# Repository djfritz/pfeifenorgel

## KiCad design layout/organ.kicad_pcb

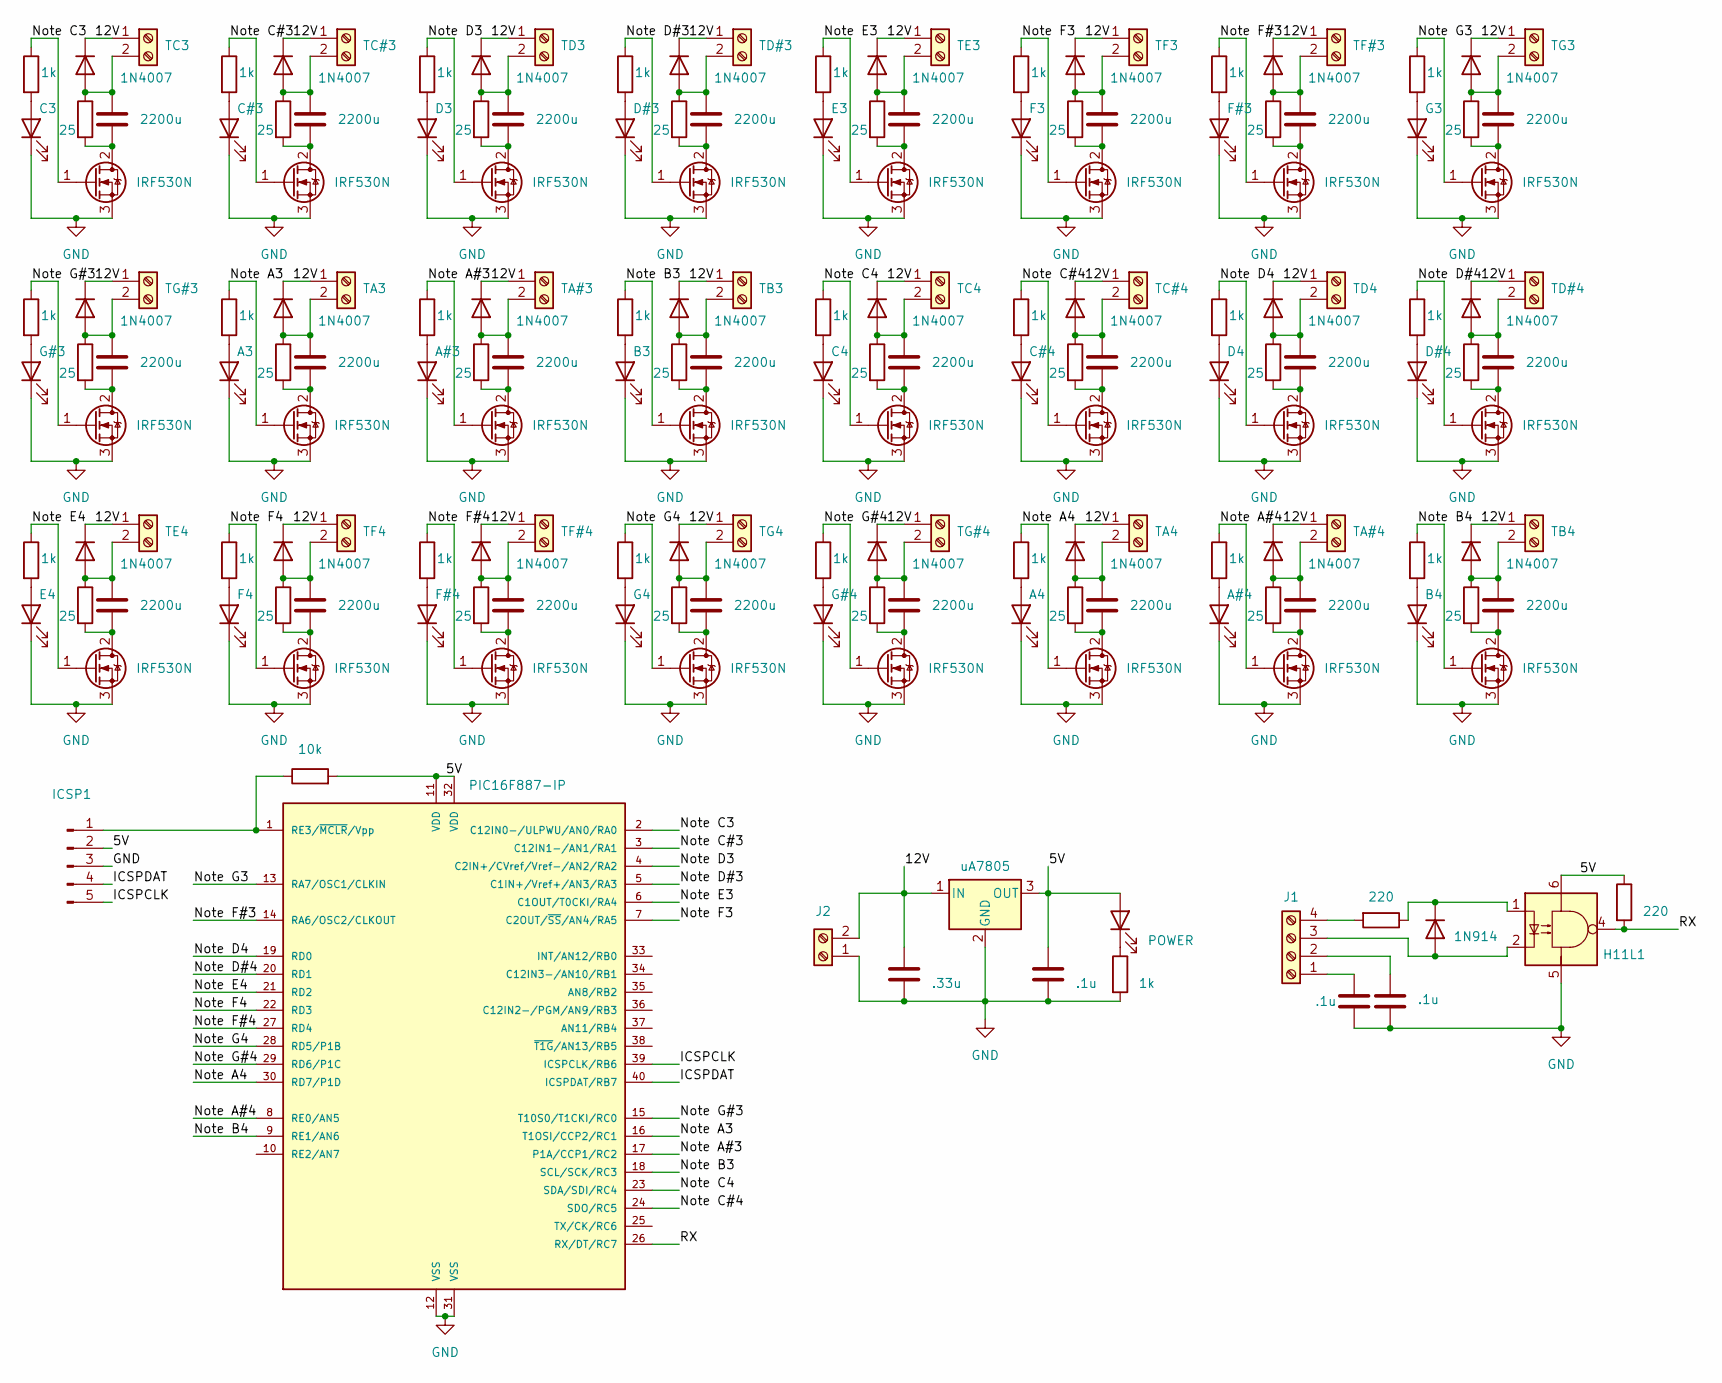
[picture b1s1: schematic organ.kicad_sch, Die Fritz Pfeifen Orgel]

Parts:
C1: .33u; C_Rect_L7.2mm_W3.0mm_P5.00mm_FKS2_FKP2_MKS2_MKP2
C2, C3, C4: .1u; C_Rect_L7.0mm_W2.5mm_P5.00mm
C5, C6, C7, C8, C9, C10, C11, C12, C13, C14, C15, C16, C17, C18, C19, C20, C21, C22, C23, C24, C25, C26, C27, C28: 2200u; C_Radial_D16.0mm_H25.0mm_P7.50mm
D1: 1N914; D_DO-35_SOD27_P7.62mm_Horizontal
D2, D6, D8, D10, D12, D14, D16, D18, D20, D22, D24, D26, D28, D30, D32, D34, D36, D38, D40, D42, D44, D46, D48, D50: 1N4007; D_DO-41_SOD81_P10.16mm_Horizontal
D3: C3; LED_D5.0mm_Clear
D4: POWER; LED_D5.0mm_Clear
D5: C#3; LED_D5.0mm_Clear
D7: D3; LED_D5.0mm_Clear
D9: D#3; LED_D5.0mm_Clear
D11: E3; LED_D5.0mm_Clear
D13: F3; LED_D5.0mm_Clear
D15: F#3; LED_D5.0mm_Clear
D17: G3; LED_D5.0mm_Clear
D19: G#3; LED_D5.0mm_Clear
D21: A3; LED_D5.0mm_Clear
D23: A#3; LED_D5.0mm_Clear
D25: B3; LED_D5.0mm_Clear
D27: C4; LED_D5.0mm_Clear
D29: C#4; LED_D5.0mm_Clear
D31: D4; LED_D5.0mm_Clear
D33: D#4; LED_D5.0mm_Clear
D35: E4; LED_D5.0mm_Clear
D37: F4; LED_D5.0mm_Clear
D39: F#4; LED_D5.0mm_Clear
D41: G4; LED_D5.0mm_Clear
D43: G#4; LED_D5.0mm_Clear
D45: A4; LED_D5.0mm_Clear
D47: A#4; LED_D5.0mm_Clear
D49: B4; LED_D5.0mm_Clear
ICSP1: Conn_01x05_Pin; PinHeader_1x05_P2.54mm_Vertical
J1: Screw_Terminal_01x04; TerminalBlock_RND_205-00003_1x04_P5.00mm_Horizontal
J2: Screw_Terminal_01x02; TerminalBlock_RND_205-00001_1x02_P5.00mm_Horizontal
Q1, Q2, Q3, Q4, Q5, Q6, Q7, Q8, Q9, Q10, Q11, Q12, Q13, Q14, Q15, Q16, Q17, Q18, Q19, Q20, Q21, Q22, Q23, Q24: IRF530N; TO-220-3_Vertical
R1, R2: 220; R_Axial_DIN0207_L6.3mm_D2.5mm_P10.16mm_Horizontal
R3: 10k; R_Axial_DIN0207_L6.3mm_D2.5mm_P10.16mm_Horizontal
R4, R8, R10, R12, R14, R16, R18, R20, R22, R24, R26, R28, R30, R32, R34, R36, R38, R40, R42, R44, R46, R48, R50, R52: 25; R_Axial_Power_L25.0mm_W9.0mm_P27.94mm
R5, R6, R7, R9, R11, R13, R15, R17, R19, R21, R23, R25, R27, R29, R31, R33, R35, R37, R39, R41, R43, R45, R47, R49, R51: 1k; R_Axial_DIN0207_L6.3mm_D2.5mm_P10.16mm_Horizontal
TA3, TA4: Screw_Terminal_01x02; TerminalBlock_RND_205-00001_1x02_P5.00mm_Horizontal
TA#3, TA#4: Screw_Terminal_01x02; TerminalBlock_RND_205-00001_1x02_P5.00mm_Horizontal
TB3, TB4: Screw_Terminal_01x02; TerminalBlock_RND_205-00001_1x02_P5.00mm_Horizontal
TC3, TC4: Screw_Terminal_01x02; TerminalBlock_RND_205-00001_1x02_P5.00mm_Horizontal
TC#3, TC#4: Screw_Terminal_01x02; TerminalBlock_RND_205-00001_1x02_P5.00mm_Horizontal
TD3, TD4: Screw_Terminal_01x02; TerminalBlock_RND_205-00001_1x02_P5.00mm_Horizontal
TD#3, TD#4: Screw_Terminal_01x02; TerminalBlock_RND_205-00001_1x02_P5.00mm_Horizontal
TE3, TE4: Screw_Terminal_01x02; TerminalBlock_RND_205-00001_1x02_P5.00mm_Horizontal
TF3, TF4: Screw_Terminal_01x02; TerminalBlock_RND_205-00001_1x02_P5.00mm_Horizontal
TF#3, TF#4: Screw_Terminal_01x02; TerminalBlock_RND_205-00001_1x02_P5.00mm_Horizontal
TG3, TG4: Screw_Terminal_01x02; TerminalBlock_RND_205-00001_1x02_P5.00mm_Horizontal
TG#3, TG#4: Screw_Terminal_01x02; TerminalBlock_RND_205-00001_1x02_P5.00mm_Horizontal
U1: uA7805; TO-220-3_Vertical
U2: H11L1; DIP-6_W7.62mm
U3: PIC16F887-IP; DIP-40_W15.24mm

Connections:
/5V: C2.1, D4.2 (A), ICSP1.2, R2.1, R3.2, U1.3 (OUT), U2.6, U3.11 (VDD), U3.32 (VDD)
/12V: C1.1, D2.1 (K), D6.1 (K), D8.1 (K), D10.1 (K), D12.1 (K), D14.1 (K), D16.1 (K), D18.1 (K), D20.1 (K), D22.1 (K), D24.1 (K), D26.1 (K), D28.1 (K), D30.1 (K), D32.1 (K), D34.1 (K), D36.1 (K), D38.1 (K), D40.1 (K), D42.1 (K), D44.1 (K), D46.1 (K), D48.1 (K), D50.1 (K), J2.2, TA3.1, TA4.1, TA#3.1, TA#4.1, TB3.1, TB4.1, TC3.1, TC4.1, TC#3.1, TC#4.1, TD3.1, TD4.1, TD#3.1, TD#4.1, TE3.1, TE4.1, TF3.1, TF4.1, TF#3.1, TF#4.1, TG3.1, TG4.1, TG#3.1, TG#4.1, U1.1 (IN)
/ICSPCLK: ICSP1.5, U3.39 (ICSPCLK/RB6)
/ICSPDAT: ICSP1.4, U3.40 (ICSPDAT/RB7)
/Note A3: Q10.1 (G), R23.1, U3.16 (T1OSI/CCP2/RC1)
/Note A4: Q22.1 (G), R47.1, U3.30 (RD7/P1D)
/Note A#3: Q11.1 (G), R25.1, U3.17 (P1A/CCP1/RC2)
/Note A#4: Q23.1 (G), R49.1, U3.8 (RE0/AN5)
/Note B3: Q12.1 (G), R27.1, U3.18 (SCL/SCK/RC3)
/Note B4: Q24.1 (G), R51.1, U3.9 (RE1/AN6)
/Note C3: Q1.1 (G), R5.1, U3.2 (C12IN0-/ULPWU/AN0/RA0)
/Note C4: Q13.1 (G), R29.1, U3.23 (SDA/SDI/RC4)
/Note C#3: Q2.1 (G), R7.1, U3.3 (C12IN1-/AN1/RA1)
/Note C#4: Q14.1 (G), R31.1, U3.24 (SDO/RC5)
/Note D3: Q3.1 (G), R9.1, U3.4 (C2IN+/CVref/Vref-/AN2/RA2)
/Note D4: Q15.1 (G), R33.1, U3.19 (RD0)
/Note D#3: Q4.1 (G), R11.1, U3.5 (C1IN+/Vref+/AN3/RA3)
/Note D#4: Q16.1 (G), R35.1, U3.20 (RD1)
/Note E3: Q5.1 (G), R13.1, U3.6 (C1OUT/T0CKI/RA4)
/Note E4: Q17.1 (G), R37.1, U3.21 (RD2)
/Note F3: Q6.1 (G), R15.1, U3.7 (C2OUT/~SS/AN4/RA5)
/Note F4: Q18.1 (G), R39.1, U3.22 (RD3)
/Note F#3: Q7.1 (G), R17.1, U3.14 (RA6/OSC2/CLKOUT)
/Note F#4: Q19.1 (G), R41.1, U3.27 (RD4)
/Note G3: Q8.1 (G), R19.1, U3.13 (RA7/OSC1/CLKIN)
/Note G4: Q20.1 (G), R43.1, U3.28 (RD5/P1B)
/Note G#3: Q9.1 (G), R21.1, U3.15 (T10S0/T1CKI/RC0)
/Note G#4: Q21.1 (G), R45.1, U3.29 (RD6/P1C)
/RX: R2.2, U2.4, U3.26 (RX/DT/RC7)
GND: C1.2, C2.2, C3.2, C4.2, D3.1 (K), D5.1 (K), D7.1 (K), D9.1 (K), D11.1 (K), D13.1 (K), D15.1 (K), D17.1 (K), D19.1 (K), D21.1 (K), D23.1 (K), D25.1 (K), D27.1 (K), D29.1 (K), D31.1 (K), D33.1 (K), D35.1 (K), D37.1 (K), D39.1 (K), D41.1 (K), D43.1 (K), D45.1 (K), D47.1 (K), D49.1 (K), ICSP1.3, J2.1, Q1.3 (S), Q2.3 (S), Q3.3 (S), Q4.3 (S), Q5.3 (S), Q6.3 (S), Q7.3 (S), Q8.3 (S), Q9.3 (S), Q10.3 (S), Q11.3 (S), Q12.3 (S), Q13.3 (S), Q14.3 (S), Q15.3 (S), Q16.3 (S), Q17.3 (S), Q18.3 (S), Q19.3 (S), Q20.3 (S), Q21.3 (S), Q22.3 (S), Q23.3 (S), Q24.3 (S), R6.2, U1.2 (GND), U2.5, U3.12 (VSS), U3.31 (VSS)
unnamed: D1.2 (A), J1.3, U2.2
unnamed: D1.1 (K), R1.1, U2.1
unnamed: C5.1, D2.2 (A), R4.1, TC3.2
unnamed: D3.2 (A), R5.2
unnamed: D4.1 (K), R6.1
unnamed: D5.2 (A), R7.2
unnamed: C6.1, D6.2 (A), R8.1, TC#3.2
unnamed: D7.2 (A), R9.2
unnamed: C7.1, D8.2 (A), R10.1, TD3.2
unnamed: D9.2 (A), R11.2
unnamed: C8.1, D10.2 (A), R12.1, TD#3.2
unnamed: D11.2 (A), R13.2
unnamed: C9.1, D12.2 (A), R14.1, TE3.2
unnamed: D13.2 (A), R15.2
unnamed: C10.1, D14.2 (A), R16.1, TF3.2
unnamed: D15.2 (A), R17.2
unnamed: C11.1, D16.2 (A), R18.1, TF#3.2
unnamed: D17.2 (A), R19.2
unnamed: C12.1, D18.2 (A), R20.1, TG3.2
unnamed: D19.2 (A), R21.2
unnamed: C13.1, D20.2 (A), R22.1, TG#3.2
unnamed: D21.2 (A), R23.2
unnamed: C14.1, D22.2 (A), R24.1, TA3.2
unnamed: D23.2 (A), R25.2
unnamed: C15.1, D24.2 (A), R26.1, TA#3.2
unnamed: D25.2 (A), R27.2
unnamed: C16.1, D26.2 (A), R28.1, TB3.2
unnamed: D27.2 (A), R29.2
unnamed: C17.1, D28.2 (A), R30.1, TC4.2
unnamed: D29.2 (A), R31.2
unnamed: C18.1, D30.2 (A), R32.1, TC#4.2
unnamed: D31.2 (A), R33.2
unnamed: C19.1, D32.2 (A), R34.1, TD4.2
unnamed: D33.2 (A), R35.2
unnamed: C20.1, D34.2 (A), R36.1, TD#4.2
unnamed: D35.2 (A), R37.2
unnamed: C21.1, D36.2 (A), R38.1, TE4.2
unnamed: D37.2 (A), R39.2
unnamed: C22.1, D38.2 (A), R40.1, TF4.2
unnamed: D39.2 (A), R41.2
unnamed: C23.1, D40.2 (A), R42.1, TF#4.2
unnamed: D41.2 (A), R43.2
unnamed: C24.1, D42.2 (A), R44.1, TG4.2
unnamed: D43.2 (A), R45.2
unnamed: C25.1, D44.2 (A), R46.1, TG#4.2
unnamed: D45.2 (A), R47.2
unnamed: C26.1, D46.2 (A), R48.1, TA4.2
unnamed: D47.2 (A), R49.2
unnamed: C27.1, D48.2 (A), R50.1, TA#4.2
unnamed: D49.2 (A), R51.2
unnamed: C28.1, D50.2 (A), R52.1, TB4.2
unnamed: ICSP1.1, R3.1, U3.1 (RE3/~MCLR/Vpp)
unnamed: C3.1, J1.1
unnamed: C4.1, J1.2
unnamed: J1.4, R1.2
unnamed: C5.2, Q1.2 (D), R4.2
unnamed: C6.2, Q2.2 (D), R8.2
unnamed: C7.2, Q3.2 (D), R10.2
unnamed: C8.2, Q4.2 (D), R12.2
unnamed: C9.2, Q5.2 (D), R14.2
unnamed: C10.2, Q6.2 (D), R16.2
unnamed: C11.2, Q7.2 (D), R18.2
unnamed: C12.2, Q8.2 (D), R20.2
unnamed: C13.2, Q9.2 (D), R22.2
unnamed: C14.2, Q10.2 (D), R24.2
unnamed: C15.2, Q11.2 (D), R26.2
unnamed: C16.2, Q12.2 (D), R28.2
unnamed: C17.2, Q13.2 (D), R30.2
unnamed: C18.2, Q14.2 (D), R32.2
unnamed: C19.2, Q15.2 (D), R34.2
unnamed: C20.2, Q16.2 (D), R36.2
unnamed: C21.2, Q17.2 (D), R38.2
unnamed: C22.2, Q18.2 (D), R40.2
unnamed: C23.2, Q19.2 (D), R42.2
unnamed: C24.2, Q20.2 (D), R44.2
unnamed: C25.2, Q21.2 (D), R46.2
unnamed: C26.2, Q22.2 (D), R48.2
unnamed: C27.2, Q23.2 (D), R50.2
unnamed: C28.2, Q24.2 (D), R52.2

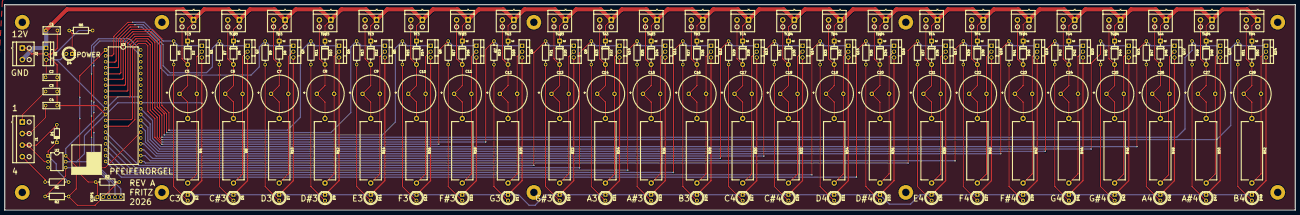
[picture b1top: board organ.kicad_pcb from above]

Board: 2 copper layers, 558.8 x 88.9 mm, 184 parts (0 on the bottom side), 109 nets.

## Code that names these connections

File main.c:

#include <xc.h>

// Configuration Bits
#pragma config FOSC = INTRC_NOCLKOUT // Oscillator Selection bits
#pragma config WDTE = OFF            // Watchdog Timer Disabled
#pragma config PWRTE = OFF           // Power-up Timer Disabled
#pragma config BOREN = ON            // Brown-out Reset Enabled
#pragma config LVP = OFF             // Low-Voltage Programming Disabled

#define _XTAL_FREQ 8000000 // Define 8 MHz crystal frequency

#define NOTEC3 48
#define NOTECS3 49
#define NOTED3 50
#define NOTEDS3 51
#define NOTEE3 52
#define NOTEF3 53
#define NOTEFS3 54
#define NOTEG3 55
#define NOTEGS3 56
#define NOTEA3 57
#define NOTEAS3 58
#define NOTEB3 59
#define NOTEC4 60
#define NOTECS4 61
#define NOTED4 62
#define NOTEDS4 63
#define NOTEE4 64
#define NOTEF4 65
#define NOTEFS4 66
#define NOTEG4 67
#define NOTEGS4 68
#define NOTEA4 69
#define NOTEAS4 70
#define NOTEB4 71

#define PC3 PORTAbits.RA0
#define PCS3 PORTAbits.RA1
#define PD3 PORTAbits.RA2
#define PDS3 PORTAbits.RA3
#define PE3 PORTAbits.RA4
#define PF3 PORTAbits.RA5
#define PFS3 PORTAbits.RA6
#define PG3 PORTAbits.RA7
#define PGS3 PORTCbits.RC0
#define PA3 PORTCbits.RC1
#define PAS3 PORTCbits.RC2
#define PB3 PORTCbits.RC3
#define PC4 PORTCbits.RC4
#define PCS4 PORTCbits.RC5
#define PD4 PORTDbits.RD0
#define PDS4 PORTDbits.RD1
#define PE4 PORTDbits.RD2
#define PF4 PORTDbits.RD3
#define PFS4 PORTDbits.RD4
#define PG4 PORTDbits.RD5
#define PGS4 PORTDbits.RD6
#define PA4 PORTDbits.RD7
#define PAS4 PORTEbits.RE0
#define PB4 PORTEbits.RE1

// MIDI parser state
//  status:    last channel status byte seen (running status), 0 == none
//  note:      first data byte (note number) of the current message
//  have_note: 1 == note captured, waiting for velocity
unsigned char status = 0;
unsigned char note = 0;
unsigned char have_note = 0;

void set_note(unsigned char n, unsigned char on) {
  if (n == NOTEC3) {
    PC3 = on;
  } else if (n == NOTECS3) {
    PCS3 = on;
  } else if (n == NOTED3) {
    PD3 = on;
  } else if (n == NOTEDS3) {
    PDS3 = on;
  } else if (n == NOTEE3) {
    PE3 = on;
  } else if (n == NOTEF3) {
    PF3 = on;
  } else if (n == NOTEFS3) {
    PFS3 = on;
  } else if (n == NOTEG3) {
    PG3 = on;
  } else if (n == NOTEGS3) {
    PGS3 = on;
  } else if (n == NOTEA3) {
    PA3 = on;
  } else if (n == NOTEAS3) {
    PAS3 = on;
  } else if (n == NOTEB3) {
    PB3 = on;
  } else if (n == NOTEC4) {
    PC4 = on;
  } else if (n == NOTECS4) {
    PCS4 = on;
  } else if (n == NOTED4) {
    PD4 = on;
  } else if (n == NOTEDS4) {
    PDS4 = on;
  } else if (n == NOTEE4) {
    PE4 = on;
  } else if (n == NOTEF4) {
    PF4 = on;
  } else if (n == NOTEFS4) {
    PFS4 = on;
  } else if (n == NOTEG4) {
    PG4 = on;
  } else if (n == NOTEGS4) {
    PGS4 = on;
  } else if (n == NOTEA4) {
    PA4 = on;
  } else if (n == NOTEAS4) {
    PAS4 = on;
  } else if (n == NOTEB4) {
    PB4 = on;
  }
}

void __interrupt() intr(void) {
  if (RCIF) {
    unsigned char data = RCREG;

    // an overrun stops the receiver until CREN is toggled
    if (OERR) {
      CREN = 0;
      CREN = 1;
    }

    // ignore real-time bytes
    if (data >= 0xF8) {
      return;
    }

    // MSB being set at all means it's a status byte, and 0xF? means it's a
    // system message (which we never care about)
    //
    // either way, if we see a status byte, we clear the note
    if (data & 0x80) {
      status = (data < 0xF0) ? data : 0;
      have_note = 0;
      return;
    }

    // data byte: we only care about note off (0x8n) and note on (0x9n)
    unsigned char type = status & 0xF0;
    if (type != 0x80 && type != 0x90) {
      return;
    }

    // second byte is the note
    if (!have_note) {
      note = data;
      have_note = 1;
      return;
    }

    // third byte is the velocity. Note on with velocity 0 is actually note off... 
    // The organ doesn't have velocity, so it's on or off
    set_note(note, (type == 0x90 && data != 0) ? 1 : 0);
    have_note = 0;
  }
};

void main(void) {
  OSCCONbits.IRCF = 0b111; // Set internal oscillator to 8 MHz
  OSCCONbits.SCS = 1;      // Select internal oscillator as system clock
  ANSEL = 0;  // Turn all digital I/O pins (disable analog functions)
  ANSELH = 0; // Clear analog high byte

  // setup and clear outputs
  TRISA = 0;
  PORTA = 0;
  TRISC0 = 0;
  TRISC1 = 0;
  TRISC2 = 0;
  TRISC3 = 0;
  TRISC4 = 0;
  TRISC5 = 0;
  PORTC = 0;
  TRISD = 0;
  PORTD = 0;
  TRISE0 = 0;
  TRISE1 = 0;
  PORTE = 0;

  // uart
  BRG16 = 0;
  SPBRGH = 0;
  SPBRG = 3; // 31250bps @ 8MHz
  RCSTAbits.CREN = 1;
  TXSTAbits.SYNC = 0;
  RCSTAbits.SPEN = 1;

  // enable interrupts
  GIE = 1;
  PEIE = 1;
  RCIE = 1;

  while (1)
    ;
}
